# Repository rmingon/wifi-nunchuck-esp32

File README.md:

# Esp32 nunchuck

# video

### Project for use a wii nunchuck on wifi or bluetooth

### 3d view

### Schematic view

### Pcb view

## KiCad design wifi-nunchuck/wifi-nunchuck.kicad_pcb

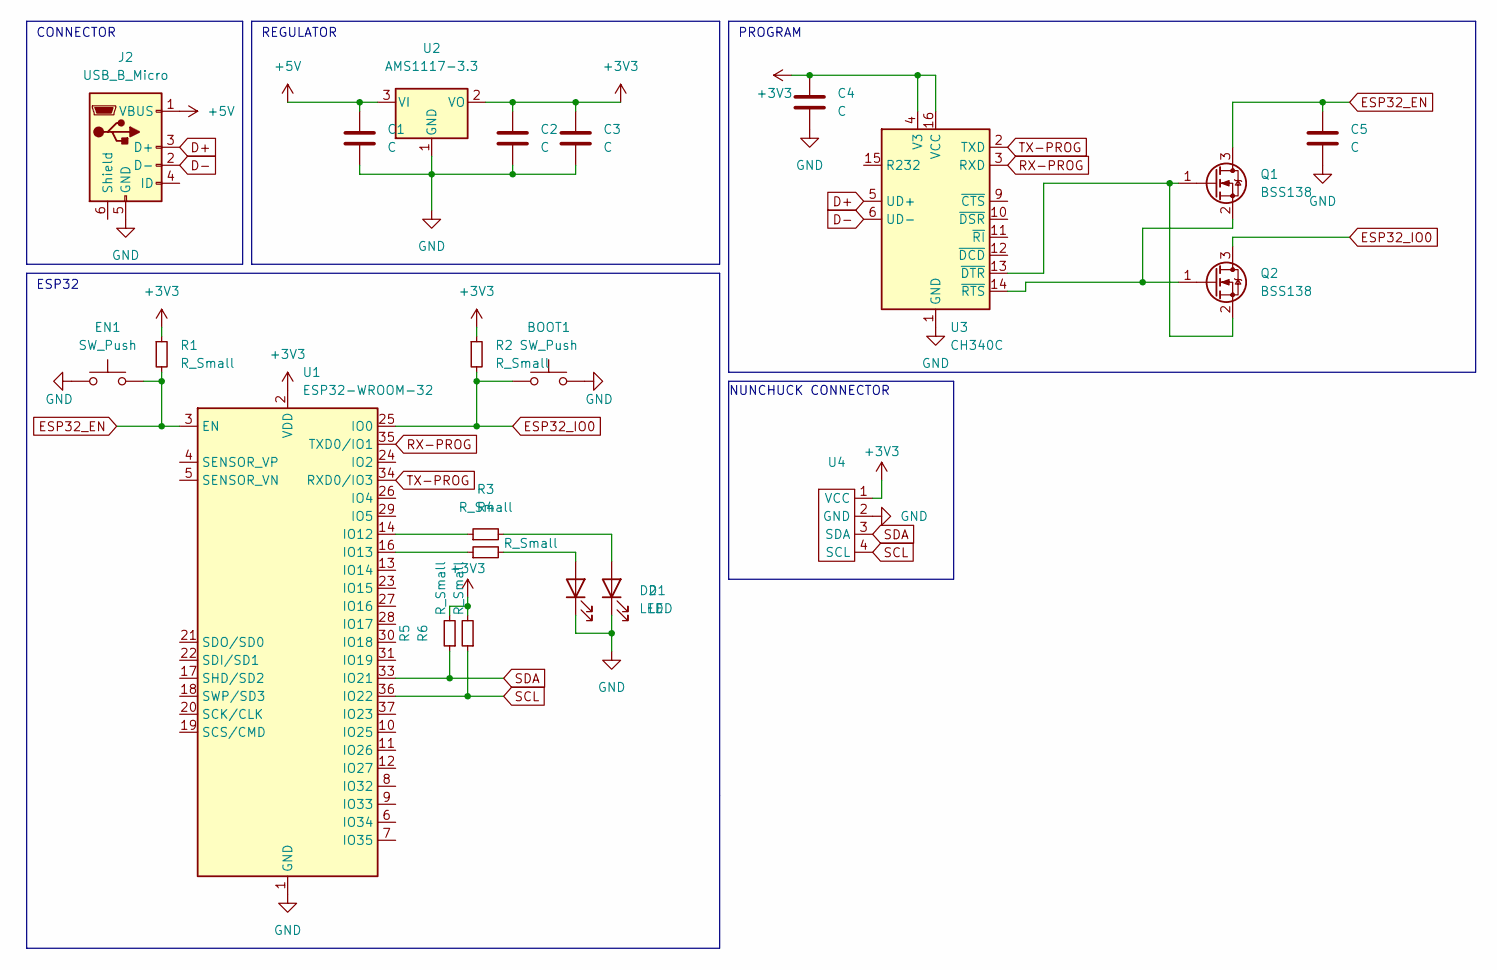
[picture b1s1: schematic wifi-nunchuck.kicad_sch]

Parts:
BOOT1: SW_Push; SW_SPST_FSMSM
C1, C2, C3, C4, C5: C; C_0603_1608Metric
D1, D2: LED; LED_0603_1608Metric
EN1: SW_Push; SW_SPST_FSMSM
J2: USB_B_Micro; USB_Micro-B_Amphenol_10118194_Horizontal
Q1, Q2: BSS138; SOT-23
R1, R2, R3, R4, R5, R6: R_Small; R_0603_1608Metric
U1: ESP32-WROOM-32
U2: AMS1117-3.3; SOT-223-3_TabPin2
U3: CH340C; SOIC-16_3.9x9.9mm_P1.27mm
U4: nunchuck

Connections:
+3V3: C2.1, C3.1, C4.1, R1.1, R2.1, R5.2, R6.2, U1.2 (VDD), U2.2 (VO), U3.4 (V3), U3.16 (VCC), U4.1 (VCC)
+5V: C1.1, J2.1 (VBUS), U2.3 (VI)
D+: J2.3 (D+), U3.5 (UD+)
D-: J2.2 (D-), U3.6 (UD-)
ESP32_EN: C5.1, EN1.2, Q1.3 (D), R1.2, U1.3 (EN)
ESP32_IO0: BOOT1.1, Q2.3 (D), R2.2, U1.25 (IO0)
GND: BOOT1.2, C1.2, C2.2, C3.2, C4.2, C5.2, D1.1 (K), D2.1 (K), EN1.1, J2.5 (GND), U1.1 (GND), U1.15 (GND), U1.38 (GND), U1.39 (GND), U2.1 (GND), U3.1 (GND), U4.2 (GND)
unnamed: D1.2 (A), R4.2
unnamed: D2.2 (A), R3.2
unnamed: Q1.1 (G), Q2.2 (S), U3.13 (~DTR)
unnamed: Q1.2 (S), Q2.1 (G), U3.14 (~RTS)
unnamed: R3.1, U1.14 (IO12)
unnamed: R4.1, U1.16 (IO13)
RX-PROG: U1.35 (TXD0/IO1), U3.3 (RXD)
SCL: R6.1, U1.36 (IO22), U4.4 (SCL)
SDA: R5.1, U1.33 (IO21), U4.3 (SDA)
TX-PROG: U1.34 (RXD0/IO3), U3.2 (TXD)

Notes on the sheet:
ESP32
NUNCHUCK CONNECTOR
REGULATOR
PROGRAM
CONNECTOR

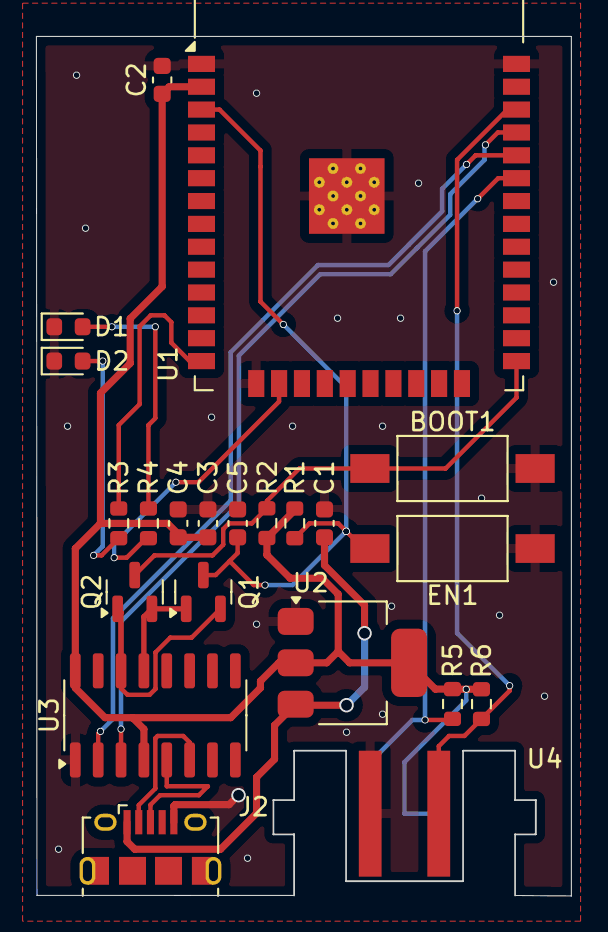
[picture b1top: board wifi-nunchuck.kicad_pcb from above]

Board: 2 copper layers, 29.7 x 47.7 mm, 22 parts (0 on the bottom side), 17 nets.

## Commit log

2024-07-26 pcb wiring
2024-07-26 add gnd plane
2024-07-26 update gnd
2024-07-26 add views
2024-07-26 add readme
2024-07-29 update plit settings
2024-08-07 first commit software
2024-08-07 add lib
2024-08-07 config vscode
2024-08-07 wifi + send data to srv
2024-08-08 add led
2024-08-09 send date when update
